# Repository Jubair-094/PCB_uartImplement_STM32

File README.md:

# PCB_uartImplement_STM32

folder uart:

1. Here, Kicad files are given. "uart.kicad_sch". This file contains a schematic. Directly opening 
  it will open the schematic editor
  
2."uart.kicad_pcb" contains the layout design. Here, all the routing is implemented. This is a 
  2-layer PCB, and by going to 3d view, can see the physical view of the PCB

folder GerberFile:

This folder contains the information related to printing the PCB. Zip the GerberFile and can upload to the website (like 'PCBWay') to print the UART PCB board

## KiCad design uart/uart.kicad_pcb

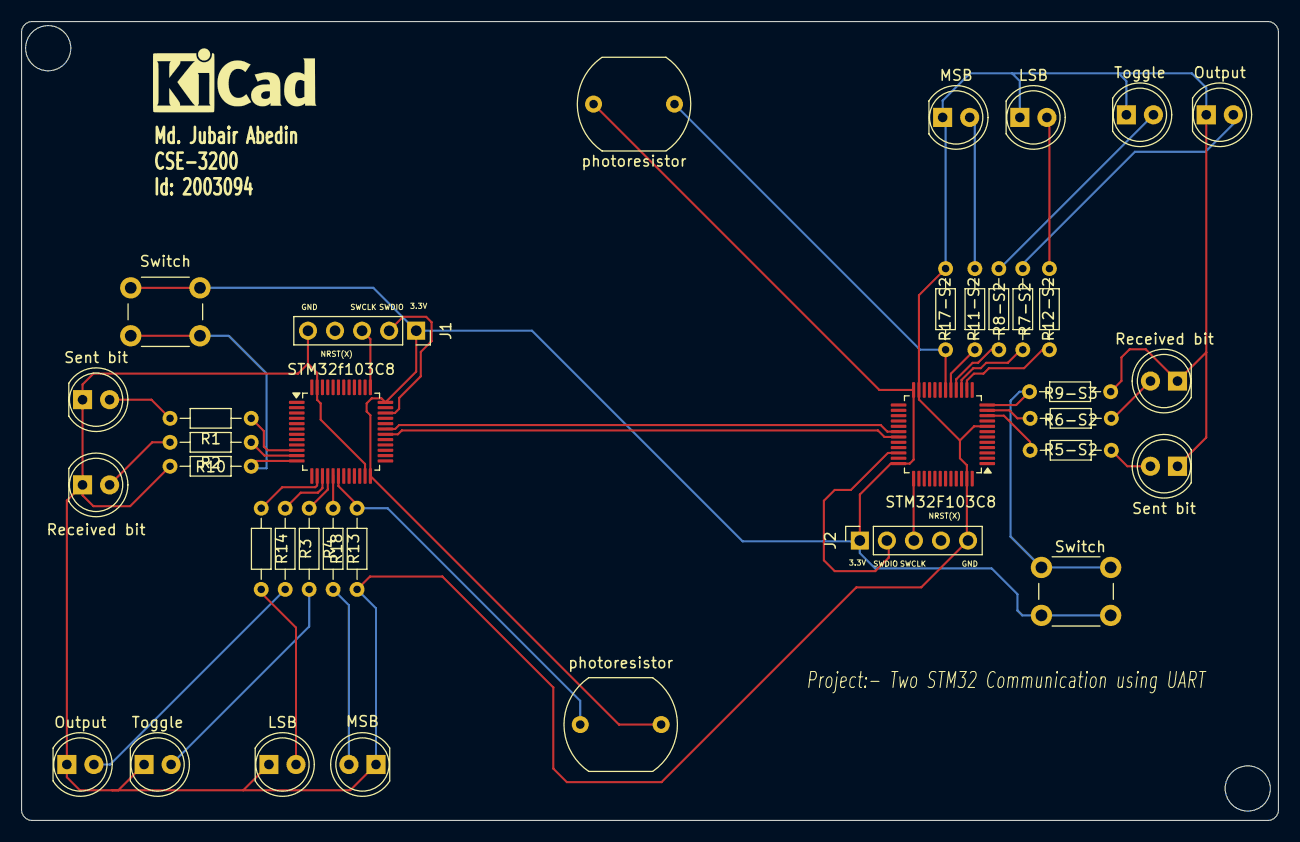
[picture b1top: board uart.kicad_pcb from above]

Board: 2 copper layers, 118.0 x 75.0 mm, 36 parts (0 on the bottom side), 36 nets.

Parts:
J1, J2: Conn_01x05; PinSocket_1x05_P2.54mm_Vertical
LSB: LED; LED_D5.0mm
LSB#2: LED; LED_D5.0mm
MSB: LED; LED_D5.0mm
MSB#2: LED; LED_D5.0mm
Output: LED; LED_D5.0mm
Output#2: LED; LED_D5.0mm
R1, R2, R3, R4, R5-S2, R6-S2, R7-S2, R8-S2, R9-S3, R10, R11-S2, R12-S2, R13, R14, R17-S2, R18: R; R_Axial_DIN0204_L3.6mm_D1.6mm_P7.62mm_Horizontal
Received bit: Received bit; LED_D5.0mm
Received bit#2: LED; LED_D5.0mm
STM32F103C8, STM32f103C8: STM32F103C6Tx; LQFP-48_7x7mm_P0.5mm
Sent bit: LED; LED_D5.0mm
Sent bit#2: LED; LED_D5.0mm
Switch: SW_Push; SW_PUSH_6mm_H5mm
Switch#2: SW_Push; SW_PUSH_6mm_H5mm
Toggle: LED; LED_D5.0mm
Toggle#2: LED; LED_D5.0mm
photoresistor: R_Photo; R_LDR_10x8.5mm_P7.6mm_Vertical
photoresistor#2: R_Photo; R_LDR_10x8.5mm_P7.6mm_Vertical

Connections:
+3.3V: J1.1, J2.1, STM32F103C8.24 (VDD), STM32F103C8.36 (VDD), STM32f103C8.24 (VDD), STM32f103C8.36 (VDD), Switch.2, Switch#2.2, photoresistor.1, photoresistor#2.1
/Blink On Receive S1: R2.2, Received bit#2.2 (A)
/Blink On Receive S2: R6-S2.2, Received bit.2 (A)
/Blink On Send S1: R1.2, Sent bit.2 (A)
/Blink On Send S2: R5-S2.2, Sent bit#2.2 (A)
/LSB data of S1: LSB#2.2 (A), R14.2
/LSB of data S2: LSB.2 (A), R12-S2.2
/MSB data by Timer S1: MSB.2 (A), R13.2
/MSB data by Timer S2: MSB#2.2 (A), R11-S2.2
/Output Photo S1: Output#2.2 (A), R3.2
/Output Photo S2: Output.2 (A), R7-S2.2
/Toggle on External Interrupt S1: R4.2, Toggle.2 (A)
/Toggle on External Interrupt S2: R8-S2.2, Toggle#2.2 (A)
GND: J1.5, J2.5, LSB.1 (K), LSB#2.1 (K), MSB.1 (K), MSB#2.1 (K), Output.1 (K), Output#2.1 (K), R9-S3.1, R10.2, R17-S2.1, R18.1, Received bit.1 (K), Received bit#2.1 (K), STM32F103C8.8 (VSSA), STM32F103C8.23 (VSS), STM32F103C8.47 (VSS), STM32f103C8.23 (VSS), STM32f103C8.47 (VSS), Sent bit.1 (K), Sent bit#2.1 (K), Toggle.1 (K), Toggle#2.1 (K)
unnamed: J1.2, STM32f103C8.34 (PA13)
unnamed: J1.3, STM32f103C8.37 (PA14)
unnamed: J2.2, STM32F103C8.34 (PA13)
unnamed: J2.3, STM32F103C8.37 (PA14)
unnamed: R1.1, STM32f103C8.10 (PA0)
unnamed: R2.1, STM32f103C8.11 (PA1)
unnamed: R10.1, STM32f103C8.12 (PA2), Switch#2.1
unnamed: R14.1, STM32f103C8.14 (PA4)
unnamed: R3.1, STM32f103C8.15 (PA5)
unnamed: R4.1, STM32f103C8.16 (PA6)
unnamed: R13.1, STM32f103C8.17 (PA7)
unnamed: STM32F103C8.31 (PA10), STM32f103C8.30 (PA9)
unnamed: STM32F103C8.30 (PA9), STM32f103C8.31 (PA10)
unnamed: R18.2, STM32f103C8.18 (PB0), photoresistor#2.2
unnamed: R5-S2.1, STM32F103C8.10 (PA0)
unnamed: R6-S2.1, STM32F103C8.11 (PA1)
unnamed: R9-S3.2, STM32F103C8.12 (PA2), Switch.1
unnamed: R12-S2.1, STM32F103C8.14 (PA4)
unnamed: R7-S2.1, STM32F103C8.15 (PA5)
unnamed: R8-S2.1, STM32F103C8.16 (PA6)
unnamed: R11-S2.1, STM32F103C8.17 (PA7)
unnamed: R17-S2.2, STM32F103C8.18 (PB0), photoresistor.2

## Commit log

2025-07-18 Create uart
2025-07-18 opening a folder to upload gerber file
2025-07-18 deleting the temp file in gerber
